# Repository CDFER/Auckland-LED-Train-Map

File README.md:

# Auckland Live LED Train Map

**You can now support my work by buying this through my store:** [**https://keastudios.co.nz/store/akl-ltm/**](https://keastudios.co.nz/store/akl-ltm/)

A physical, real-time LED map of the Auckland train network, powered by an ESP32-C3 microcontroller. Train movements are displayed using addressable RGB LEDs, with live data fetched over Wi-Fi.

---

## Table of Contents

- [Auckland Live LED Train Map](#auckland-live-led-train-map)
  - [Table of Contents](#table-of-contents)
  - [Features](#features)
  - [Hardware](#hardware)
  - [PCB Design](#pcb-design)
  - [Software / Firmware](#software--firmware)
  - [Getting Started](#getting-started)
  - [Web Installer](#web-installer)
  - [Links](#links)
  - [Contributing](#contributing)
  - [License](#license)

---

## Features

- **Real-time Train Tracking:** Displays the approximate locations of trains on the Auckland network.
- **Addressable LEDs:** ~150 WS2812B-compatible RGB LEDs (1.6x1.5mm) for a vibrant display.
- **Wi-Fi Connectivity:** ESP32-C3's built-in Wi-Fi fetches live train data.
- **Custom PCB:** Designed for JLCPCB manufacturing limits.
- **Open Source:** Hardware and firmware are open source.

---

## Hardware

- **Microcontroller:** ESP32-C3 (RISC-V, 160 MHz, 4 MB Flash, QFN32)
- **LEDs:** ~150 x XL-1615RGBC-WS2812B (1.6mm x 1.5mm)
- **PCB:** 249mm x 66mm, JLCPCB-friendly
- **Antenna:** On-board PCB antenna ([TI CC2430DB design](https://www.ti.com/lit/ug/swru125/swru125.pdf))

---

## PCB Design

- Designed in **KiCad V9.0** using [JLCPCB KiCad Library](https://github.com/CDFER/jlcpcb-kicad-library)
- **View Online:** [Interactive PCB Layout (Kicanvas)](https://kicanvas.org/?github=https%3A%2F%2Fgithub.com%2FCDFER%2FAuckland-LED-Train-Map%2Ftree%2Fmain%2FPCB)
- **Source Files:** `/PCB` directory

---

## Software / Firmware

The firmware has been moved to it own repo now and can be found here: [LED-Rails-Firmware](https://github.com/CDFER/LED-Rails-Firmware)

---

## Getting Started

1. **Flash the Firmware:**
   - Use the [Web Installer](https://cdfer.github.io/LED-Rails-Firmware/led-rails.html) (recommended, no drivers needed)
2. **Connect to Wi-Fi:**
   - On first boot, use the web interface to configure Wi-Fi credentials.
3. **Power the Board:**
   - Use a 5V USB-C power supply capable of at least 1A.
4. **Enjoy the Live Map!**

---

## Web Installer

Easily flash the latest firmware to your ESP32-C3 using your browser:

[Open the LED Rails Web Installer](https://cdfer.github.io/LED-Rails-Firmware/led-rails.html)

- Works with Chrome, Edge, or any Web Serial-compatible browser
- Follow on-screen instructions to connect and flash your device

---

## Links

- [Web Installer](https://cdfer.github.io/LED-Rails-Firmware/led-rails.html)
- [Interactive PCB Viewer](https://kicanvas.org/?github=https%3A%2F%2Fgithub.com%2FCDFER%2FAuckland-LED-Train-Map%2Ftree%2Fmain%2FPCB)
- [GTFS Realtime Cache API](https://github.com/CDFER/GTFS-Realtime-Cache-Server)
- [JLCPCB KiCad Library](https://github.com/CDFER/jlcpcb-kicad-library)

---

## Contributing

Contributions are welcome! Open an issue or submit a pull request for improvements, bug fixes, or feature suggestions.

---

## License

This project is released under the GPL-3.0-or-later license.

© 2025 Chris Dirks

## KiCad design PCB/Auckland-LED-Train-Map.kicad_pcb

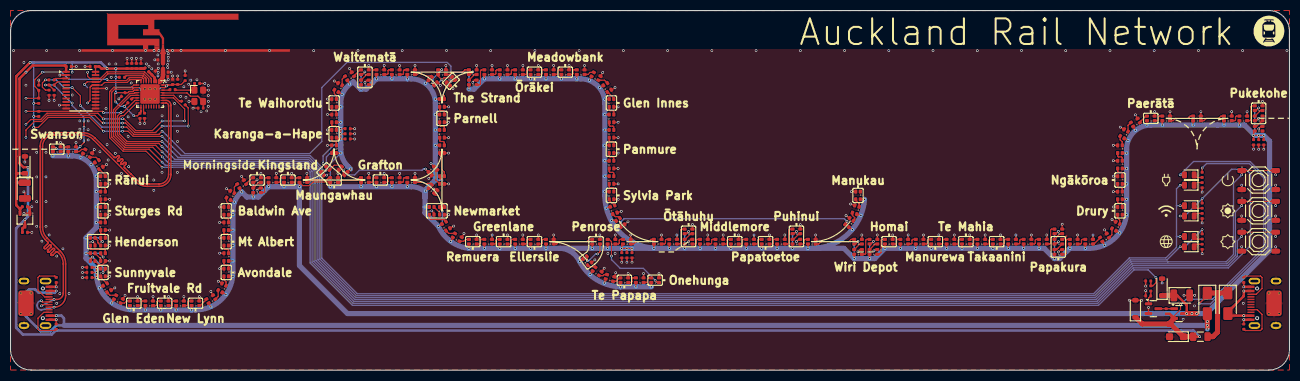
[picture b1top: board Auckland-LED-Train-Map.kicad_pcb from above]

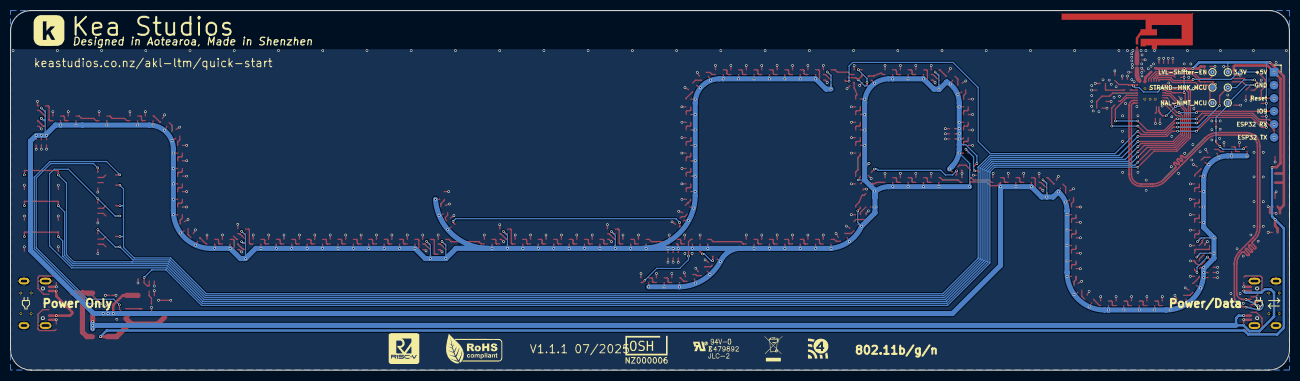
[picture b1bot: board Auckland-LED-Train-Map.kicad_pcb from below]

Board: 2 copper layers, 249.0 x 70.0 mm, 248 parts (7 on the bottom side), 199 nets.

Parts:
AE1: Antenna_Shield; Inverted_F_Antenna_2.4Ghz_1.0mmPCB_TI_CC2430DB.pretty
C1: 10uF; C_CASE-A-3216-18(mm)
C2, C3, C4, C6, C7, C8, C9, C10, C11, C12, C13, C14, C18, C21, C22, C25, C26, C27, C28, C29, C30, C31, C35, C38, C39, C40, C41, C42, C43: 1uF; C_0402
C5, C15: 100uF; C_CASE-B-3528-21(mm)
C19, C20: 27pF; C_0402
C36, C37: 1.5pF; C_0402
D1: MMSZ5227B; D_SOD-123
D2, D10, D11: Red; D_0805
D4, D5: MM1W5V6; D_SOD-123
D6, D7: SS54; D_SMA
D8, D9, D12: Green; D_0805
D13: H3V3U10B; D_DFN1006-2L
D100, D101, D102, D103, D104, D105, D106, D107, D108, D109, D110, D111, D112, D113, D114, D115, D116, D117, D118, D119, D120, D121, D122, D123, D124, D125, D126, D127, D128, D129, D130, D131, D132, D133, D134, D135, D136, D137, D138, D139, D140, D141, D142, D143, D144, D145, D146, D147, D148, D149, D150, D151, D152, D153, D154, D155, D156, D157, D158, D159, D160, D161, D162, D163, D164, D165, D166, D167, D168, D169, D170, D171, D172, D173, D174, D175, D176, D177, D178, D179, D180, D181, D182, D183, D184, D185, D186, D187, D188, D189, D190, D191, D192, D193, D194, D195, D196, D197, D198, D199, D200, D201, D202, D203, D204, D205, D206, D207, D208, D300, D301, D302, D303, D304, D305, D306, D307, D308, D309, D310, D311, D312, D313, D314, D315, D316, D317, D318, D319, D320, D321, D322, D323, D324, D325, D326, D327, D328, D329, D330, D331, D332, D333, D334, D335, D336, D337, D338, D339, D340, D341, D342, D343, D344: XL-1615RGBC-WS2812B-S; LED-SMD_4P-L1.6-W1.5_XL-1615RGBC-WS2812B
F1: Polyfuse, 2A; Fuse_1206_3216Metric
J1: Prog Connector
L1, L3: 2.7nH; L_0402
L5: 15nH,300mA; L_0402
LOGO1: OSHW-Certification-Mark-Stacked_8x7mm_SilkMask
Q1: HL3415A; Q_SOT-23
Q2: MMBT3904; Q_SOT-23
R1, R2, R3, R4, R8, R12, R17, R21: 10kΩ; R_0402
R7, R18: 510Ω; R_0402
R9, R16, R22, R23, R24, R25: 100kΩ; R_0402
R10, R15: 100Ω; R_0402
R13, R14, R19, R20: 5.1kΩ; R_0402
S1, S2, S3: Tactile Button, 160gf; SW-SMD_4P-L5.1-W5.1-P3.70-LS6.5-TL-2
TP2: NAL-NIMT_MCU; TestPoint_Pad_D1.0mm
TP3: NAL-NIMT_LED; TestPoint_Pad_D1.0mm
TP8: STRAND-MNK_MCU; TestPoint_Pad_D1.0mm
TP9: STRAND-MNK_LED; TestPoint_Pad_D1.0mm
TP13: 3.3V; TestPoint_Pad_D1.0mm
TP15: LVL-Shifter-EN; TestPoint_Pad_D1.0mm
U1: XC6206P332MR; SOT-23-3_L2.9-W1.6-P1.90-LS2.8-BR
U2: ESP32-C3FH4; QFN-32-1EP_5x5mm_P0.5mm_EP3.7x3.7mm_ThermalVias
U3: SN74LVC4245APWR; TSSOP-24_4.4x7.8mm_P0.65mm
U4, U5: Connector, USB-TYPE-C-16P; TYPE-C-SMD_HX-TYPE-C-16PIN
X1: 40MHz, 15pF; OSC-SMD_4P-L3.2-W2.5-BL_SIT8008BI

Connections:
+3V3: C3.1, C4.1, C5.1, C6.1, C8.1, C9.1, C10.1, C11.1, C12.1, C13.1, C22.1, C25.1, D1.1, D8.2, D10.2, D11.2, L3.1, R1.1, R2.1, R3.1, R4.1, TP13.1, U1.2 (VOUT), U2.11 (VDD3P3_RTC), U2.17 (VDD3P3_CPU), U2.31 (VDDA), U2.32 (VDDA), U3.23 (VCCB(3V)), U3.24 (VCCB(3V))
+5V: C15.1, C26.1, C27.1, C28.1, C29.1, C30.1, C31.1, C38.1, C39.1, C40.1, C41.1, C42.1, C43.1, D4.1, D100.2 (VDD), D101.2 (VDD), D102.2 (VDD), D103.2 (VDD), D104.2 (VDD), D105.2 (VDD), D106.2 (VDD), D107.2 (VDD), D108.2 (VDD), D109.2 (VDD), D110.2 (VDD), D111.2 (VDD), D112.2 (VDD), D113.2 (VDD), D114.2 (VDD), D115.2 (VDD), D116.2 (VDD), D117.2 (VDD), D118.2 (VDD), D119.2 (VDD), D120.2 (VDD), D121.2 (VDD), D122.2 (VDD), D123.2 (VDD), D124.2 (VDD), D125.2 (VDD), D126.2 (VDD), D127.2 (VDD), D128.2 (VDD), D129.2 (VDD), D130.2 (VDD), D131.2 (VDD), D132.2 (VDD), D133.2 (VDD), D134.2 (VDD), D135.2 (VDD), D136.2 (VDD), D137.2 (VDD), D138.2 (VDD), D139.2 (VDD), D140.2 (VDD), D141.2 (VDD), D142.2 (VDD), D143.2 (VDD), D144.2 (VDD), D145.2 (VDD), D146.2 (VDD), D147.2 (VDD), D148.2 (VDD), D149.2 (VDD), D150.2 (VDD), D151.2 (VDD), D152.2 (VDD), D153.2 (VDD), D154.2 (VDD), D155.2 (VDD), D156.2 (VDD), D157.2 (VDD), D158.2 (VDD), D159.2 (VDD), D160.2 (VDD), D161.2 (VDD), D162.2 (VDD), D163.2 (VDD), D164.2 (VDD), D165.2 (VDD), D166.2 (VDD), D167.2 (VDD), D168.2 (VDD), D169.2 (VDD), D170.2 (VDD), D171.2 (VDD), D172.2 (VDD), D173.2 (VDD), D174.2 (VDD), D175.2 (VDD), D176.2 (VDD), D177.2 (VDD), D178.2 (VDD), D179.2 (VDD), D180.2 (VDD), D181.2 (VDD), D182.2 (VDD), D183.2 (VDD), D184.2 (VDD), D185.2 (VDD), D186.2 (VDD), D187.2 (VDD), D188.2 (VDD), D189.2 (VDD), D190.2 (VDD), D191.2 (VDD), D192.2 (VDD), D193.2 (VDD), D194.2 (VDD), D195.2 (VDD), D196.2 (VDD), D197.2 (VDD), D198.2 (VDD), D199.2 (VDD), D200.2 (VDD), D201.2 (VDD), D202.2 (VDD), D203.2 (VDD), D204.2 (VDD), D205.2 (VDD), D206.2 (VDD), D207.2 (VDD), D208.2 (VDD), D300.2 (VDD), D301.2 (VDD), D302.2 (VDD), D303.2 (VDD), D304.2 (VDD), D305.2 (VDD), D306.2 (VDD), D307.2 (VDD), D308.2 (VDD), D309.2 (VDD), D310.2 (VDD), D311.2 (VDD), D312.2 (VDD), D313.2 (VDD), D314.2 (VDD), D315.2 (VDD), D316.2 (VDD), D317.2 (VDD), D318.2 (VDD), D319.2 (VDD), D320.2 (VDD), D321.2 (VDD), D322.2 (VDD), D323.2 (VDD), D324.2 (VDD), D325.2 (VDD), D326.2 (VDD), D327.2 (VDD), D328.2 (VDD), D329.2 (VDD), D330.2 (VDD), D331.2 (VDD), D332.2 (VDD), D333.2 (VDD), D334.2 (VDD), D335.2 (VDD), D336.2 (VDD), D337.2 (VDD), D338.2 (VDD), D339.2 (VDD), D340.2 (VDD), D341.2 (VDD), D342.2 (VDD), D343.2 (VDD), D344.2 (VDD), Q1.3 (D)
/+BRIGHTNESS_BUTTON: S2.1 (A), S2.2 (B), U2.13 (MTDO)
/-BRIGHTNESS_BUTTON: S3.1 (A), S3.2 (B), U2.12 (MTCK)
/Antenna: C36.1, D13.2, L1.1, U2.1 (LNA_IN)
/BOOT_IO9_BUTTON: J1.4, R1.2, S1.1 (A), S1.2 (B), U2.15 (GPIO9)
/CONFIG_LED: D12.2, R21.1, U2.10 (MTDI)
/D+: U2.26 (GPIO19/USB_D+), U4.A6 (D+), U4.B6 (D+)
/D-: U2.25 (GPIO18/USB_D-), U4.A7 (D-), U4.B7 (D-)
/LED_+5V_EN_Active_High: R17.1, R18.1, U2.9 (MTMS)
/LVL_Shifter_EN_Active_Low: TP15.1, U2.4 (GPIO0/XTAL_32K_P), U3.22 (OE#)
/MCU_RX: J1.5, U2.27 (U0RXD)
/MCU_TX: J1.6, R7.1
/NAL-NIMT_MCU: TP2.1, U2.8 (GPIO3), U3.20 (B2)
/Reset: C14.1, J1.3, R4.2, U2.7 (CHIP_EN)
/STRAND-MNK_MCU: TP8.1, U2.5 (GPIO1/XTAL_32K_N), U3.21 (B1)
/WIFI_LED: D9.2, R8.1, U2.16 (GPIO10)
GND: AE1.2 (Shield), C1.2, C2.2, C3.2, C4.2, C5.2, C6.2, C7.2, C8.2, C9.2, C10.2, C11.2, C12.2, C13.2, C14.2, C15.2, C18.2, C19.1, C20.2, C21.2, C22.2, C25.2, C26.2, C27.2, C28.2, C29.2, C30.2, C31.2, C35.2, C36.2, C37.2, C38.2, C39.2, C40.2, C41.2, C42.2, C43.2, D1.2, D4.2, D5.2, D13.1, D100.3 (GND), D101.3 (GND), D102.3 (GND), D103.3 (GND), D104.3 (GND), D105.3 (GND), D106.3 (GND), D107.3 (GND), D108.3 (GND), D109.3 (GND), D110.3 (GND), D111.3 (GND), D112.3 (GND), D113.3 (GND), D114.3 (GND), D115.3 (GND), D116.3 (GND), D117.3 (GND), D118.3 (GND), D119.3 (GND), D120.3 (GND), D121.3 (GND), D122.3 (GND), D123.3 (GND), D124.3 (GND), D125.3 (GND), D126.3 (GND), D127.3 (GND), D128.3 (GND), D129.3 (GND), D130.3 (GND), D131.3 (GND), D132.3 (GND), D133.3 (GND), D134.3 (GND), D135.3 (GND), D136.3 (GND), D137.3 (GND), D138.3 (GND), D139.3 (GND), D140.3 (GND), D141.3 (GND), D142.3 (GND), D143.3 (GND), D144.3 (GND), D145.3 (GND), D146.3 (GND), D147.3 (GND), D148.3 (GND), D149.3 (GND), D150.3 (GND), D151.3 (GND), D152.3 (GND), D153.3 (GND), D154.3 (GND), D155.3 (GND), D156.3 (GND), D157.3 (GND), D158.3 (GND), D159.3 (GND), D160.3 (GND), D161.3 (GND), D162.3 (GND), D163.3 (GND), D164.3 (GND), D165.3 (GND), D166.3 (GND), D167.3 (GND), D168.3 (GND), D169.3 (GND), D170.3 (GND), D171.3 (GND), D172.3 (GND), D173.3 (GND), D174.3 (GND), D175.3 (GND), D176.3 (GND), D177.3 (GND), D178.3 (GND), D179.3 (GND), D180.3 (GND), D181.3 (GND), D182.3 (GND), D183.3 (GND), D184.3 (GND), D185.3 (GND), D186.3 (GND), D187.3 (GND), D188.3 (GND), D189.3 (GND), D190.3 (GND), D191.3 (GND), D192.3 (GND), D193.3 (GND), D194.3 (GND), D195.3 (GND), D196.3 (GND), D197.3 (GND), D198.3 (GND), D199.3 (GND), D200.3 (GND), D201.3 (GND), D202.3 (GND), D203.3 (GND), D204.3 (GND), D205.3 (GND), D206.3 (GND), D207.3 (GND), D208.3 (GND), D300.3 (GND), D301.3 (GND), D302.3 (GND), D303.3 (GND), D304.3 (GND), D305.3 (GND), D306.3 (GND), D307.3 (GND), D308.3 (GND), D309.3 (GND), D310.3 (GND), D311.3 (GND), D312.3 (GND), D313.3 (GND), D314.3 (GND), D315.3 (GND), D316.3 (GND), D317.3 (GND), D318.3 (GND), D319.3 (GND), D320.3 (GND), D321.3 (GND), D322.3 (GND), D323.3 (GND), D324.3 (GND), D325.3 (GND), D326.3 (GND), D327.3 (GND), D328.3 (GND), D329.3 (GND), D330.3 (GND), D331.3 (GND), D332.3 (GND), D333.3 (GND), D334.3 (GND), D335.3 (GND), D336.3 (GND), D337.3 (GND), D338.3 (GND), D339.3 (GND), D340.3 (GND), D341.3 (GND), D342.3 (GND), D343.3 (GND), D344.3 (GND), J1.2, Q2.2 (E), R9.2, R13.2, R14.2, R17.2, R19.2, R20.2, R22.2, R23.2, R24.2, R25.2, S1.3 (C), S1.4 (D), S2.3 (C), S2.4 (D), S3.3 (C), S3.4 (D), U1.1 (GND), U2.33 (GND), U3.2 (DIR), U3.11 (GND), U3.12 (GND), U3.13 (GND), U3.14 (B8), U3.15 (B7), U3.16 (B6), U3.17 (B5), U3.18 (B4), U3.19 (B3), U4.A12B1 (GND), U4.B12A1 (GND), U4.S1 (SHIELD), U5.A12B1 (GND), U5.B12A1 (GND), U5.S1 (SHIELD), X1.2 (GND), X1.4 (GND)
NAL-NIMT-1: D100.4 (DIN), R10.1, R24.1, TP3.1
NAL-NIMT-2: D135.1 (DOUT), D136.4 (DIN)
NAL-NIMT-3: D165.1 (DOUT), D166.4 (DIN)
NAL-NIMT-4: D192.1 (DOUT), D193.4 (DIN)
unnamed: AE1.1 (A), C37.1, L1.2
unnamed: C7.1, L3.2, U2.2 (VDD3P3), U2.3 (VDD3P3)
unnamed: C20.1, L5.1, X1.1 (OSC)
unnamed: D2.1, R12.1
unnamed: D2.2, D6.1, D7.1, F1.1
unnamed: D6.2, U4.A9B4 (VBUS), U4.B9A4 (VBUS)
unnamed: D7.2, U5.A9B4 (VBUS), U5.B9A4 (VBUS)
unnamed: D8.1, R9.1
unnamed: D9.1, R22.1
unnamed: D10.1, R8.2
unnamed: D11.1, R21.2
unnamed: D12.1, R23.1
unnamed: D100.1 (DOUT), D101.4 (DIN)
unnamed: D101.1 (DOUT), D102.4 (DIN)
unnamed: D102.1 (DOUT), D103.4 (DIN)
unnamed: D103.1 (DOUT), D104.4 (DIN)
unnamed: D104.1 (DOUT), D105.4 (DIN)
unnamed: D105.1 (DOUT), D106.4 (DIN)
unnamed: D106.1 (DOUT), D107.4 (DIN)
unnamed: D107.1 (DOUT), D108.4 (DIN)
unnamed: D108.1 (DOUT), D109.4 (DIN)
unnamed: D109.1 (DOUT), D110.4 (DIN)
unnamed: D110.1 (DOUT), D111.4 (DIN)
unnamed: D111.1 (DOUT), D112.4 (DIN)
unnamed: D112.1 (DOUT), D113.4 (DIN)
unnamed: D113.1 (DOUT), D114.4 (DIN)
unnamed: D114.1 (DOUT), D115.4 (DIN)
unnamed: D115.1 (DOUT), D116.4 (DIN)
unnamed: D116.1 (DOUT), D117.4 (DIN)
unnamed: D117.1 (DOUT), D118.4 (DIN)
unnamed: D118.1 (DOUT), D119.4 (DIN)
unnamed: D119.1 (DOUT), D120.4 (DIN)
unnamed: D120.1 (DOUT), D121.4 (DIN)
unnamed: D121.1 (DOUT), D122.4 (DIN)
unnamed: D122.1 (DOUT), D123.4 (DIN)
unnamed: D123.1 (DOUT), D124.4 (DIN)
unnamed: D124.1 (DOUT), D125.4 (DIN)
unnamed: D125.1 (DOUT), D126.4 (DIN)
unnamed: D126.1 (DOUT), D127.4 (DIN)
unnamed: D127.1 (DOUT), D128.4 (DIN)
unnamed: D128.1 (DOUT), D129.4 (DIN)
unnamed: D129.1 (DOUT), D130.4 (DIN)
unnamed: D130.1 (DOUT), D131.4 (DIN)
unnamed: D131.1 (DOUT), D132.4 (DIN)
unnamed: D132.1 (DOUT), D133.4 (DIN)
unnamed: D133.1 (DOUT), D134.4 (DIN)
unnamed: D134.1 (DOUT), D135.4 (DIN)
unnamed: D136.1 (DOUT), D137.4 (DIN)
unnamed: D137.1 (DOUT), D138.4 (DIN)
unnamed: D138.1 (DOUT), D139.4 (DIN)
unnamed: D139.1 (DOUT), D140.4 (DIN)
unnamed: D140.1 (DOUT), D141.4 (DIN)
unnamed: D141.1 (DOUT), D142.4 (DIN)
unnamed: D142.1 (DOUT), D143.4 (DIN)
unnamed: D143.1 (DOUT), D144.4 (DIN)
unnamed: D144.1 (DOUT), D145.4 (DIN)
unnamed: D145.1 (DOUT), D146.4 (DIN)
unnamed: D146.1 (DOUT), D147.4 (DIN)
unnamed: D147.1 (DOUT), D148.4 (DIN)
unnamed: D148.1 (DOUT), D149.4 (DIN)
unnamed: D149.1 (DOUT), D150.4 (DIN)
unnamed: D150.1 (DOUT), D151.4 (DIN)
unnamed: D152.1 (DOUT), D153.4 (DIN)
unnamed: D153.1 (DOUT), D154.4 (DIN)
unnamed: D154.1 (DOUT), D155.4 (DIN)
unnamed: D155.1 (DOUT), D156.4 (DIN)
unnamed: D157.1 (DOUT), D158.4 (DIN)
unnamed: D158.1 (DOUT), D159.4 (DIN)
unnamed: D159.1 (DOUT), D160.4 (DIN)
unnamed: D160.1 (DOUT), D161.4 (DIN)
unnamed: D161.1 (DOUT), D162.4 (DIN)
unnamed: D162.1 (DOUT), D163.4 (DIN)
unnamed: D163.1 (DOUT), D164.4 (DIN)
unnamed: D164.1 (DOUT), D165.4 (DIN)
unnamed: D166.1 (DOUT), D167.4 (DIN)
unnamed: D167.1 (DOUT), D168.4 (DIN)
unnamed: D168.1 (DOUT), D169.4 (DIN)
unnamed: D169.1 (DOUT), D170.4 (DIN)
unnamed: D170.1 (DOUT), D171.4 (DIN)
unnamed: D171.1 (DOUT), D172.4 (DIN)
unnamed: D172.1 (DOUT), D173.4 (DIN)
unnamed: D173.1 (DOUT), D174.4 (DIN)
unnamed: D174.1 (DOUT), D175.4 (DIN)
unnamed: D175.1 (DOUT), D176.4 (DIN)
unnamed: D176.1 (DOUT), D177.4 (DIN)
unnamed: D177.1 (DOUT), D178.4 (DIN)
unnamed: D178.1 (DOUT), D179.4 (DIN)
unnamed: D179.1 (DOUT), D180.4 (DIN)
unnamed: D180.1 (DOUT), D181.4 (DIN)
unnamed: D181.1 (DOUT), D182.4 (DIN)
unnamed: D182.1 (DOUT), D183.4 (DIN)
unnamed: D183.1 (DOUT), D184.4 (DIN)
unnamed: D184.1 (DOUT), D185.4 (DIN)
unnamed: D185.1 (DOUT), D186.4 (DIN)
unnamed: D186.1 (DOUT), D187.4 (DIN)
unnamed: D187.1 (DOUT), D188.4 (DIN)
unnamed: D188.1 (DOUT), D189.4 (DIN)
unnamed: D189.1 (DOUT), D190.4 (DIN)
unnamed: D190.1 (DOUT), D191.4 (DIN)
unnamed: D191.1 (DOUT), D192.4 (DIN)
unnamed: D193.1 (DOUT), D194.4 (DIN)
unnamed: D194.1 (DOUT), D195.4 (DIN)
unnamed: D195.1 (DOUT), D196.4 (DIN)
unnamed: D196.1 (DOUT), D197.4 (DIN)
unnamed: D197.1 (DOUT), D198.4 (DIN)
unnamed: D198.1 (DOUT), D199.4 (DIN)
unnamed: D199.1 (DOUT), D200.4 (DIN)
unnamed: D200.1 (DOUT), D201.4 (DIN)
unnamed: D201.1 (DOUT), D202.4 (DIN)
unnamed: D202.1 (DOUT), D203.4 (DIN)
unnamed: D203.1 (DOUT), D204.4 (DIN)
unnamed: D204.1 (DOUT), D205.4 (DIN)
unnamed: D205.1 (DOUT), D206.4 (DIN)
unnamed: D206.1 (DOUT), D207.4 (DIN)
unnamed: D207.1 (DOUT), D208.4 (DIN)
unnamed: D300.1 (DOUT), D301.4 (DIN)
unnamed: D301.1 (DOUT), D302.4 (DIN)
unnamed: D302.1 (DOUT), D303.4 (DIN)
unnamed: D303.1 (DOUT), D304.4 (DIN)
unnamed: D304.1 (DOUT), D305.4 (DIN)
unnamed: D305.1 (DOUT), D306.4 (DIN)
unnamed: D306.1 (DOUT), D307.4 (DIN)
unnamed: D307.1 (DOUT), D308.4 (DIN)
unnamed: D308.1 (DOUT), D309.4 (DIN)
unnamed: D309.1 (DOUT), D310.4 (DIN)
unnamed: D310.1 (DOUT), D311.4 (DIN)
unnamed: D311.1 (DOUT), D312.4 (DIN)
unnamed: D312.1 (DOUT), D313.4 (DIN)
unnamed: D313.1 (DOUT), D314.4 (DIN)
unnamed: D314.1 (DOUT), D315.4 (DIN)
unnamed: D315.1 (DOUT), D316.4 (DIN)
unnamed: D316.1 (DOUT), D317.4 (DIN)
unnamed: D317.1 (DOUT), D318.4 (DIN)
unnamed: D318.1 (DOUT), D319.4 (DIN)
unnamed: D319.1 (DOUT), D320.4 (DIN)
unnamed: D320.1 (DOUT), D321.4 (DIN)
unnamed: D321.1 (DOUT), D322.4 (DIN)
unnamed: D322.1 (DOUT), D323.4 (DIN)
unnamed: D323.1 (DOUT), D324.4 (DIN)
unnamed: D324.1 (DOUT), D325.4 (DIN)
unnamed: D325.1 (DOUT), D326.4 (DIN)
unnamed: D326.1 (DOUT), D327.4 (DIN)
unnamed: D327.1 (DOUT), D328.4 (DIN)
unnamed: D328.1 (DOUT), D329.4 (DIN)
unnamed: D329.1 (DOUT), D330.4 (DIN)
unnamed: D330.1 (DOUT), D331.4 (DIN)
unnamed: D331.1 (DOUT), D332.4 (DIN)
unnamed: D332.1 (DOUT), D333.4 (DIN)
unnamed: D333.1 (DOUT), D334.4 (DIN)
unnamed: D334.1 (DOUT), D335.4 (DIN)
unnamed: D335.1 (DOUT), D336.4 (DIN)
unnamed: D336.1 (DOUT), D337.4 (DIN)
unnamed: D337.1 (DOUT), D338.4 (DIN)
unnamed: D338.1 (DOUT), D339.4 (DIN)
unnamed: D339.1 (DOUT), D340.4 (DIN)
unnamed: D341.1 (DOUT), D342.4 (DIN)
unnamed: D342.1 (DOUT), D343.4 (DIN)
unnamed: D343.1 (DOUT), D344.4 (DIN)
unnamed: Q1.1 (G), Q2.3 (C), R16.2
unnamed: C35.1, Q2.1 (B), R18.2
unnamed: R3.2, U2.6 (GPIO2)
unnamed: R2.2, U2.14 (GPIO8)
unnamed: R7.2, U2.28 (U0TXD)
unnamed: C19.2, U2.29 (XTAL_N), X1.3 (OSC)
unnamed: L5.2, U2.30 (XTAL_P)
unnamed: R15.2, U3.3 (A1)
unnamed: R10.2, U3.4 (A2)
unnamed: R13.1, U4.A5 (CC1)
unnamed: R14.1, U4.B5 (CC2)
unnamed: R20.1, U5.A5 (CC1)
unnamed: R19.1, U5.B5 (CC2)
Onehunga Branch End: D156.1 (DOUT), D157.4 (DIN)
Onehunga Branch Start: D151.1 (DOUT), D152.4 (DIN)
STRAND-MNK-1: D300.4 (DIN), R15.1, R25.1, TP9.1
STRAND-MNK-2: D340.1 (DOUT), D341.4 (DIN)
VBUS: C1.1, C2.1, C21.1, D5.1, F1.2, J1.1, Q1.2 (S), R12.2, R16.1, U1.3 (VIN), U3.1 (VCCA(5V))
VDD_SPI: C18.1, U2.18 ((OUTPUT)_VDD_SPI)

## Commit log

2025-06-07 PCB Checkpoint
2025-06-09 Update README, Update settings and improve Wi-Fi connection handling
2025-06-15 Finish V1.1 PCB
2025-06-15 Adjust component attributes for BOM exclusion
2025-11-04 Remove firmware folder and update readme

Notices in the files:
PCB/Auckland-LED-Train-Map.kicad_pcb:
©Chris Dirks
README.md:
Hardware, Software and Documentation License: GPL-3.0-or-later
